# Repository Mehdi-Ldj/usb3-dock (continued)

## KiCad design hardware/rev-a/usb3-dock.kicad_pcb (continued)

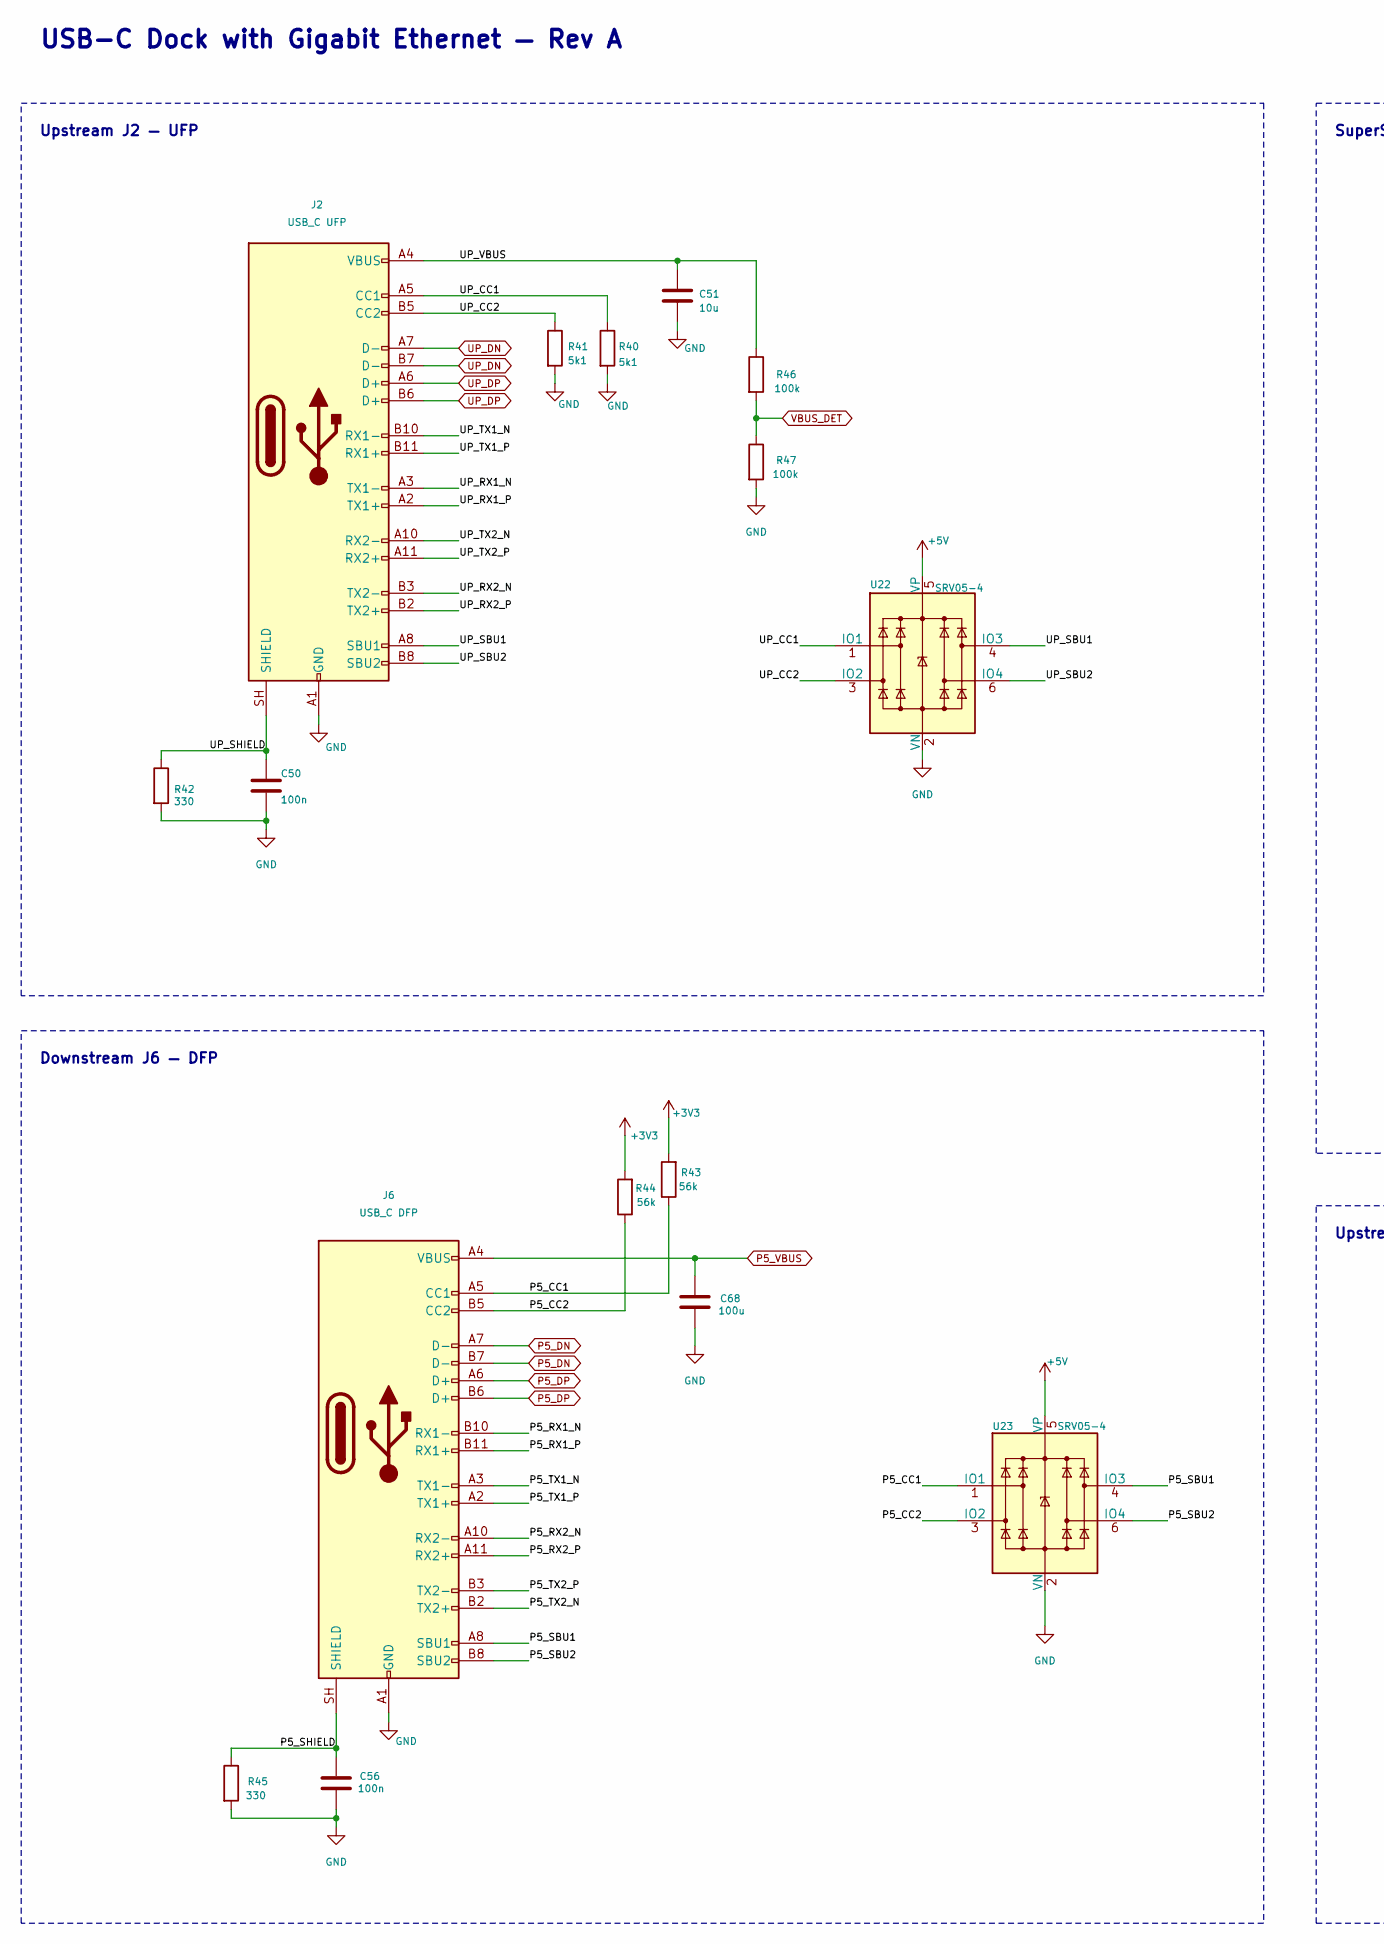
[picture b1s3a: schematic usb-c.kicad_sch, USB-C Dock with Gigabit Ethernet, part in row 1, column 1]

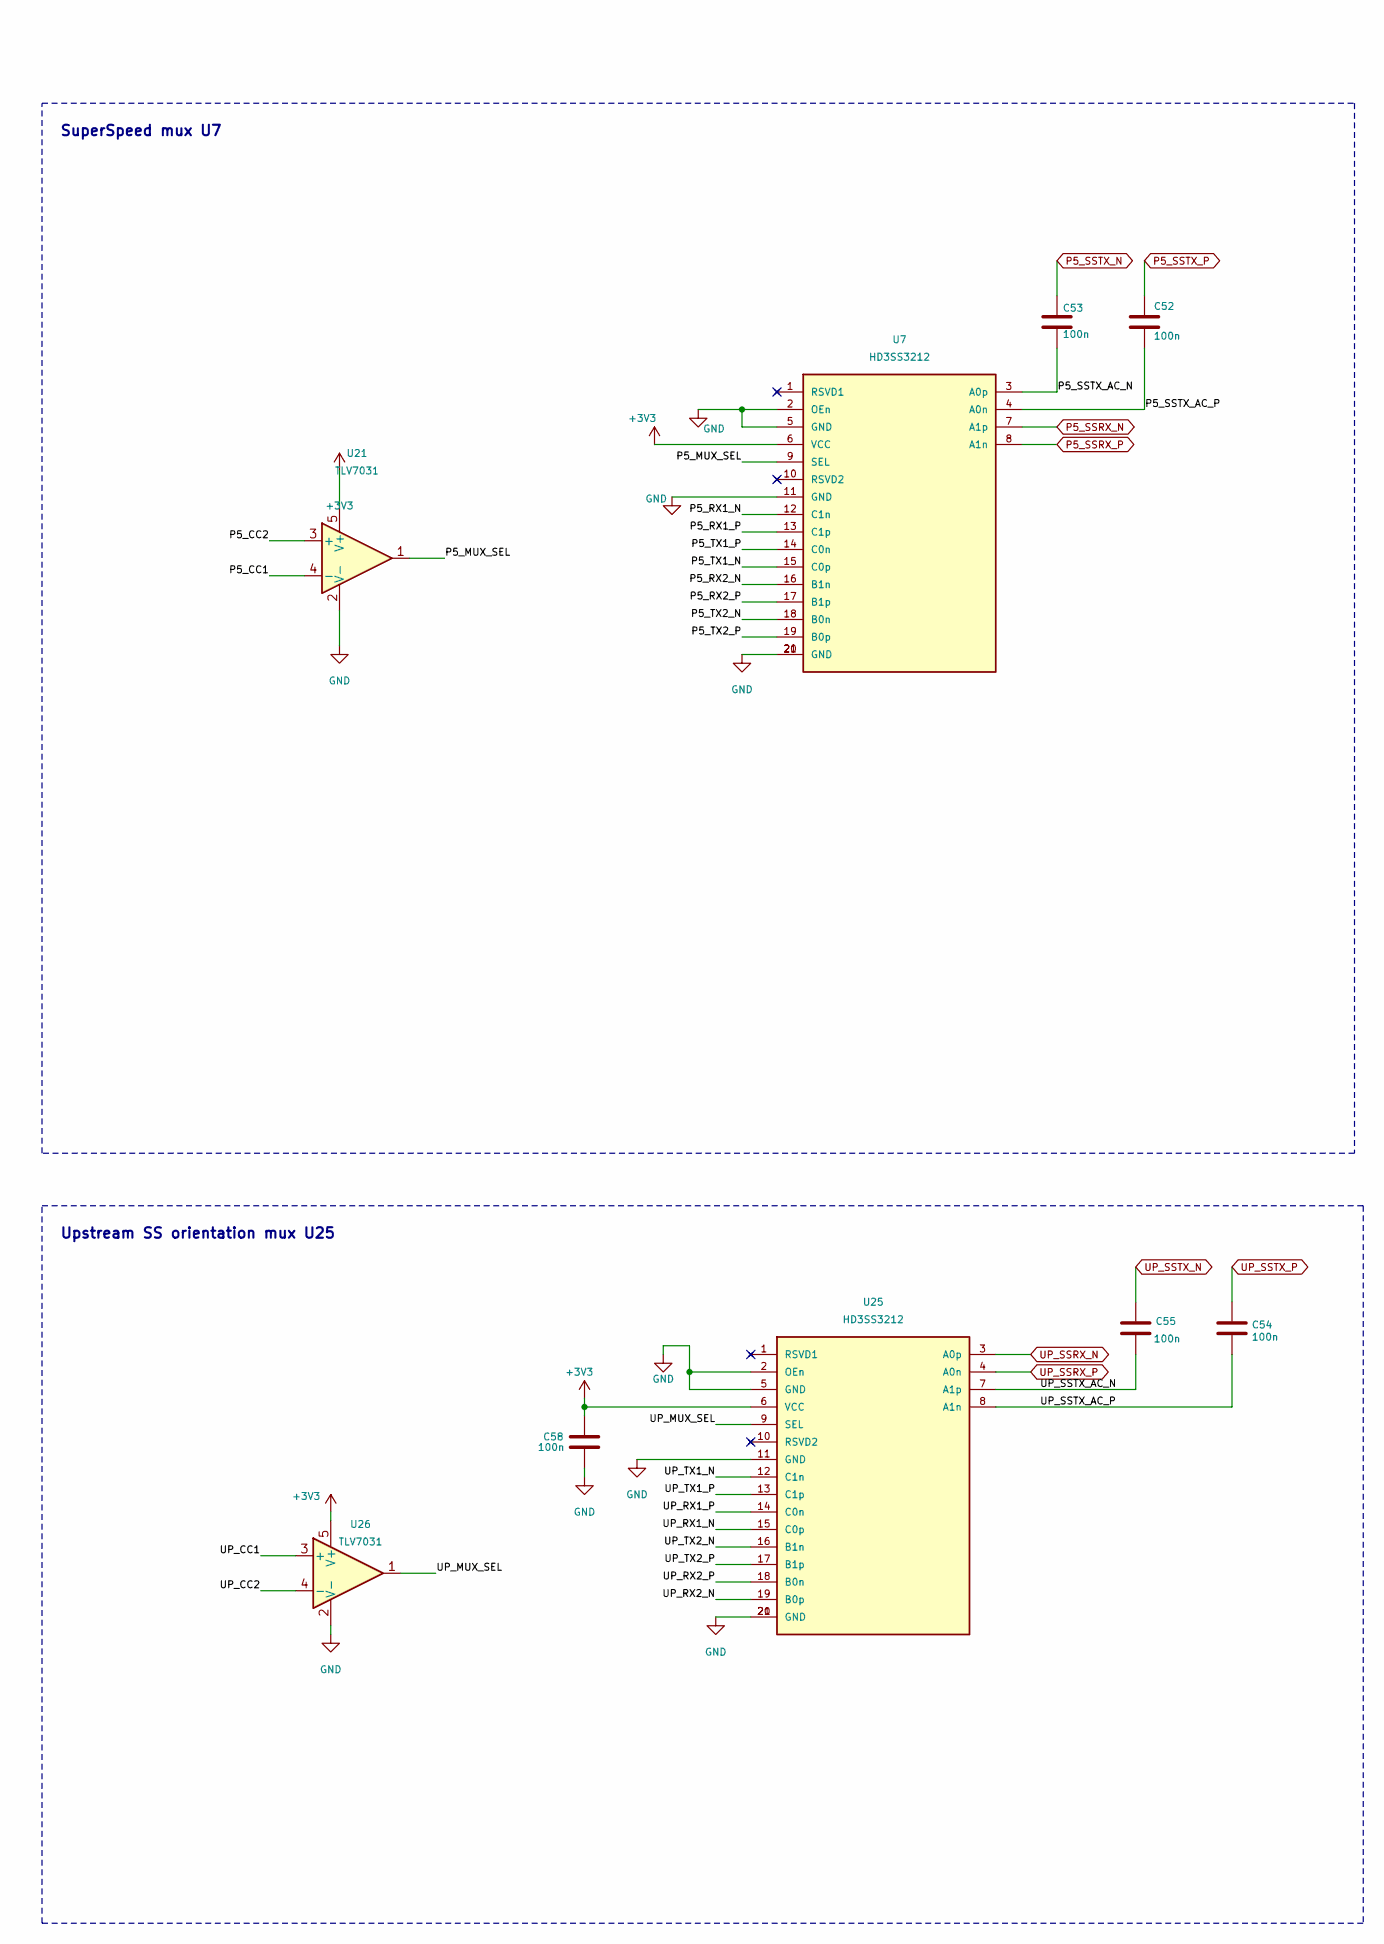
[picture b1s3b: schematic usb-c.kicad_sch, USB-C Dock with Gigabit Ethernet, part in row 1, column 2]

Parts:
C50, C52, C53, C54, C55, C56, C58: 100n; C_0402_1005Metric
C51: 10u; C_0805_2012Metric
C68: 100u; C_1210_3225Metric
J2: USB_C UFP; USB_C_Receptacle_Amphenol_12401610E4-2A
J6: USB_C DFP; USB_C_Receptacle_Amphenol_12401610E4-2A
R40, R41: 5k1; R_0603_1608Metric
R42, R45: 330; R_0603_1608Metric
R43, R44: 56k; R_0603_1608Metric
R46, R47: 100k; R_0603_1608Metric
U7, U25: HD3SS3212; DHVQFN-20-1EP_2.5x4.5mm_P0.5mm_EP1x3mm_TI
U21, U26: TLV7031; SOT-23-5
U22, U23: SRV05-4; SOT-23-6

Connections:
+3V3: C58.1, R43.2, R44.2, U7.6 (VCC), U21.5 (V+), U25.6 (VCC), U26.5 (V+); also elsewhere on the board
+5V: U22.5 (VP), U23.5 (VP); also elsewhere on the board
/usb-c/P5_CC1: J6.A5 (CC1), R43.1, U21.4 (-), U23.1 (IO1)
/usb-c/P5_CC2: J6.B5 (CC2), R44.1, U21.3 (+), U23.3 (IO2)
/usb-c/P5_MUX_SEL: U7.9 (SEL), U21.1
/usb-c/P5_RX1_N: J6.B10 (RX1-), U7.12 (C1n)
/usb-c/P5_RX1_P: J6.B11 (RX1+), U7.13 (C1p)
/usb-c/P5_RX2_N: J6.A10 (RX2-), U7.16 (B1n)
/usb-c/P5_RX2_P: J6.A11 (RX2+), U7.17 (B1p)
/usb-c/P5_SBU1: J6.A8 (SBU1), U23.4 (IO3)
/usb-c/P5_SBU2: J6.B8 (SBU2), U23.6 (IO4)
/usb-c/P5_SHIELD: C56.1, J6.SH (SHIELD), R45.1
/usb-c/P5_SSTX_AC_N: C53.2, U7.3 (A0p)
/usb-c/P5_SSTX_AC_P: C52.2, U7.4 (A0n)
/usb-c/P5_TX1_N: J6.A3 (TX1-), U7.15 (C0p)
/usb-c/P5_TX1_P: J6.A2 (TX1+), U7.14 (C0n)
/usb-c/P5_TX2_N: J6.B2 (TX2+), U7.18 (B0n)
/usb-c/P5_TX2_P: J6.B3 (TX2-), U7.19 (B0p)
/usb-c/UP_CC1: J2.A5 (CC1), R40.1, U22.1 (IO1), U26.3 (+)
/usb-c/UP_CC2: J2.B5 (CC2), R41.1, U22.3 (IO2), U26.4 (-)
/usb-c/UP_MUX_SEL: U25.9 (SEL), U26.1
/usb-c/UP_RX1_N: J2.A3 (TX1-), U25.15 (C0p)
/usb-c/UP_RX1_P: J2.A2 (TX1+), U25.14 (C0n)
/usb-c/UP_RX2_N: J2.B3 (TX2-), U25.19 (B0p)
/usb-c/UP_RX2_P: J2.B2 (TX2+), U25.18 (B0n)
/usb-c/UP_SBU1: J2.A8 (SBU1), U22.4 (IO3)
/usb-c/UP_SBU2: J2.B8 (SBU2), U22.6 (IO4)
/usb-c/UP_SHIELD: C50.1, J2.SH (SHIELD), R42.1
/usb-c/UP_SSTX_AC_N: C55.2, U25.7 (A1p)
/usb-c/UP_SSTX_AC_P: C54.2, U25.8 (A1n)
/usb-c/UP_TX1_N: J2.B10 (RX1-), U25.12 (C1n)
/usb-c/UP_TX1_P: J2.B11 (RX1+), U25.13 (C1p)
/usb-c/UP_TX2_N: J2.A10 (RX2-), U25.16 (B1n)
/usb-c/UP_TX2_P: J2.A11 (RX2+), U25.17 (B1p)
/usb-c/UP_VBUS: C51.1, J2.A4 (VBUS), J2.A9 (VBUS), J2.B4 (VBUS), J2.B9 (VBUS), R46.1
GND: C50.2, C51.2, C56.2, C58.2, C68.2, J2.A1 (GND), J2.A12 (GND), J2.B1 (GND), J2.B12 (GND), J6.A1 (GND), J6.A12 (GND), J6.B1 (GND), J6.B12 (GND), R40.2, R41.2, R42.2, R45.2, R47.2, U7.2 (OEn), U7.5 (GND), U7.11 (GND), U7.20 (GND), U7.21 (GND), U21.2 (V-), U22.2 (VN), U23.2 (VN), U25.2 (OEn), U25.5 (GND), U25.11 (GND), U25.20 (GND), U25.21 (GND), U26.2 (V-); also elsewhere on the board
P5_DN: J6.A7 (D-), J6.B7 (D-); also elsewhere on the board
P5_DP: J6.A6 (D+), J6.B6 (D+); also elsewhere on the board
P5_SSRX_N: U7.7 (A1p); also elsewhere on the board
P5_SSRX_P: U7.8 (A1n); also elsewhere on the board
P5_SSTX_N: C53.1; also elsewhere on the board
P5_SSTX_P: C52.1; also elsewhere on the board
P5_VBUS: C68.1, J6.A4 (VBUS), J6.A9 (VBUS), J6.B4 (VBUS), J6.B9 (VBUS); also elsewhere on the board
UP_DN: J2.A7 (D-), J2.B7 (D-); also elsewhere on the board
UP_DP: J2.A6 (D+), J2.B6 (D+); also elsewhere on the board
UP_SSRX_N: U25.3 (A0p); also elsewhere on the board
UP_SSRX_P: U25.4 (A0n); also elsewhere on the board
UP_SSTX_N: C55.1; also elsewhere on the board
UP_SSTX_P: C54.1; also elsewhere on the board
VBUS_DET: R46.2, R47.1; also elsewhere on the board

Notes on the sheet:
Downstream J6 — DFP
Upstream J2 — UFP
USB-C Dock with Gigabit Ethernet — Rev A
SuperSpeed mux U7
Upstream SS orientation mux U25

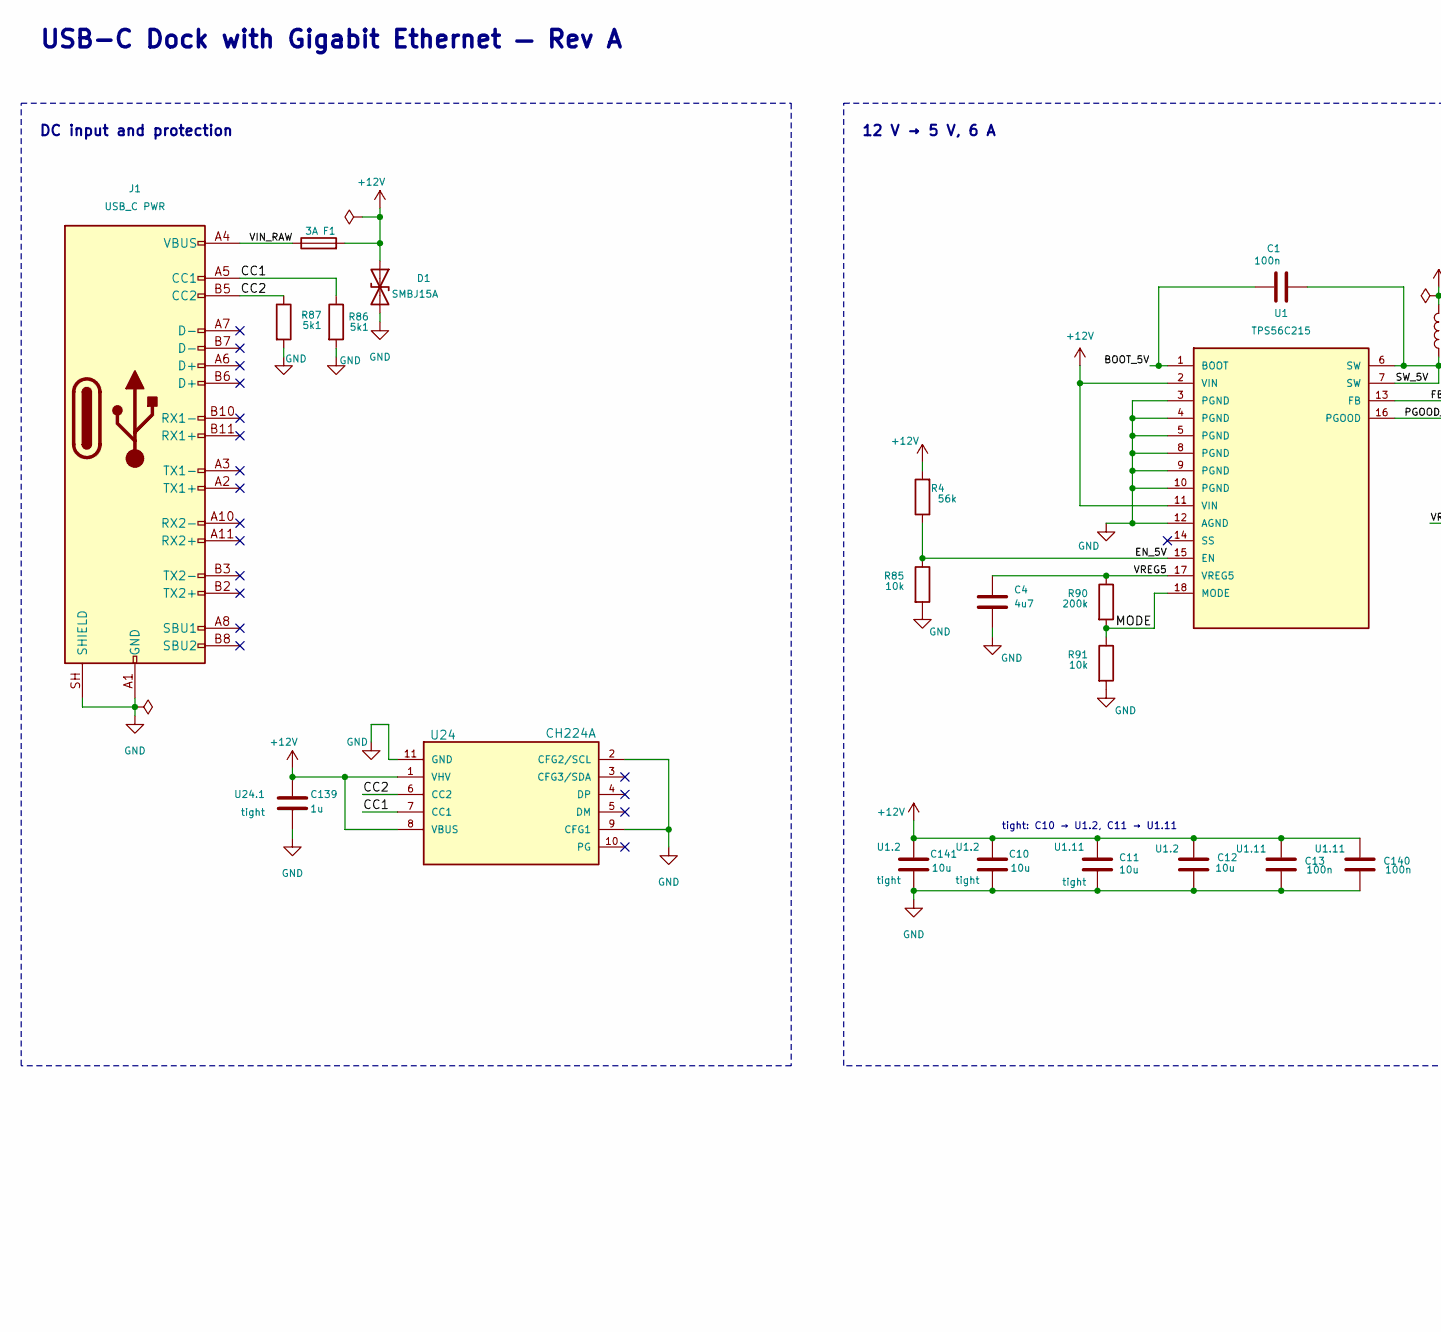
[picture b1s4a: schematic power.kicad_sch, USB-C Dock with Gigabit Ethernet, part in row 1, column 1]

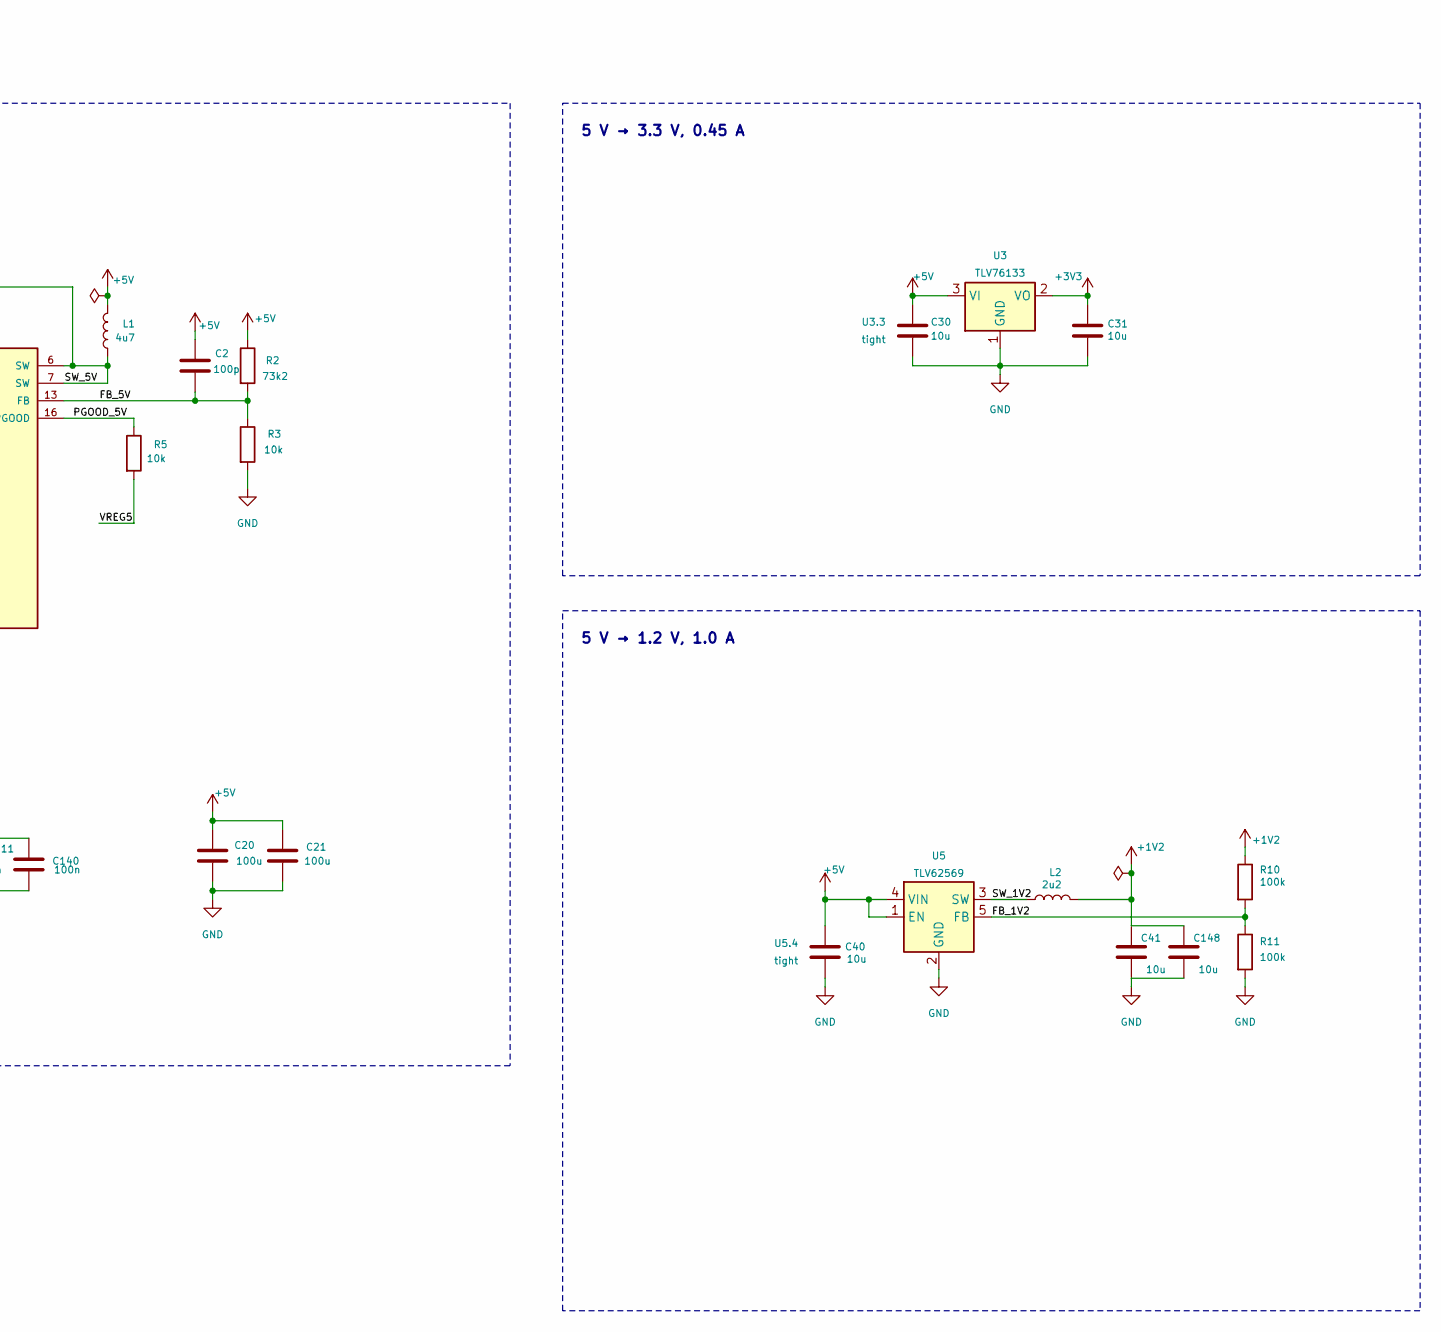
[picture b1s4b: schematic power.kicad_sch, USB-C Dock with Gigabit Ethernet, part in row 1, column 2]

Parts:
C1, C13, C140: 100n; C_0402_1005Metric
C2: 100p; C_0402_1005Metric
C4: 4u7; C_0603_1608Metric
C10, C11, C12, C30, C31, C40, C41, C141, C148: 10u; C_0805_2012Metric
C20, C21: 100u; C_1210_3225Metric
C139: 1u; C_0805_2012Metric
D1: SMBJ15A; D_SMB
F1: 3A; Fuse_1206_3216Metric
J1: USB_C PWR; USB_C_Receptacle_Amphenol_12401610E4-2A
L1: 4u7; L_7.1x6.6mm_CMLO0650H
L2: 2u2; L_4x4mm_PNR4020
R2: 73k2; R_0603_1608Metric
R3, R5, R85, R91: 10k; R_0603_1608Metric
R4: 56k; R_0603_1608Metric
R10, R11: 100k; R_0603_1608Metric
R86, R87: 5k1; R_0603_1608Metric
R90: 200k; R_0603_1608Metric
U1: TPS56C215; Texas_RNN0018A_TPS56C215
U3: TLV76133; SOT-223-3_TabPin2
U5: TLV62569; SOT-23-5
U24: CH224A; SSOP-10-1EP_3.9x4.9mm_P1mm_EP2.1x3.3mm

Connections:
+1V2: C41.1, C148.1, L2.2, R10.1; also elsewhere on the board
+3V3: C31.1, U3.2 (VO); also elsewhere on the board
+5V: C2.1, C20.1, C21.1, C30.1, C40.1, L1.2, R2.1, U3.3 (VI), U5.1 (EN), U5.4 (VIN); also elsewhere on the board
+12V: C10.1, C11.1, C12.1, C13.1, C139.1, C140.1, C141.1, D1.1 (A1), F1.2, R4.2, U1.2 (VIN), U1.11 (VIN), U24.1 (VHV), U24.8 (VBUS)
/power/BOOT_5V: C1.1, U1.1 (BOOT)
/power/CC1: J1.A5 (CC1), R86.1, U24.7 (CC1)
/power/CC2: J1.B5 (CC2), R87.1, U24.6 (CC2)
/power/EN_5V: R4.1, R85.1, U1.15 (EN)
/power/FB_1V2: R10.2, R11.1, U5.5 (FB)
/power/FB_5V: C2.2, R2.2, R3.1, U1.13 (FB)
/power/MODE: R90.2, R91.1, U1.18 (MODE)
/power/PGOOD_5V: R5.1, U1.16 (PGOOD)
/power/SW_1V2: L2.1, U5.3 (SW)
/power/SW_5V: C1.2, L1.1, U1.6 (SW), U1.7 (SW)
/power/VIN_RAW: F1.1, J1.A4 (VBUS), J1.A9 (VBUS), J1.B4 (VBUS), J1.B9 (VBUS)
/power/VREG5: C4.1, R5.2, R90.1, U1.17 (VREG5)
GND: C4.2, C10.2, C11.2, C12.2, C13.2, C20.2, C21.2, C30.2, C31.2, C40.2, C41.2, C139.2, C140.2, C141.2, C148.2, D1.2 (A2), J1.A1 (GND), J1.A12 (GND), J1.B1 (GND), J1.B12 (GND), J1.SH (SHIELD), R3.2, R11.2, R85.2, R86.2, R87.2, R91.2, U1.3 (PGND), U1.4 (PGND), U1.5 (PGND), U1.8 (PGND), U1.9 (PGND), U1.10 (PGND), U1.12 (AGND), U3.1 (GND), U5.2 (GND), U24.2 (CFG2/SCL), U24.9 (CFG1), U24.11 (GND); also elsewhere on the board

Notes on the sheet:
USB-C Dock with Gigabit Ethernet — Rev A
12 V → 5 V, 6 A
tight: C10 → U1.2, C11 → U1.11
5 V → 3.3 V, 0.45 A
5 V → 1.2 V, 1.0 A
DC input and protection

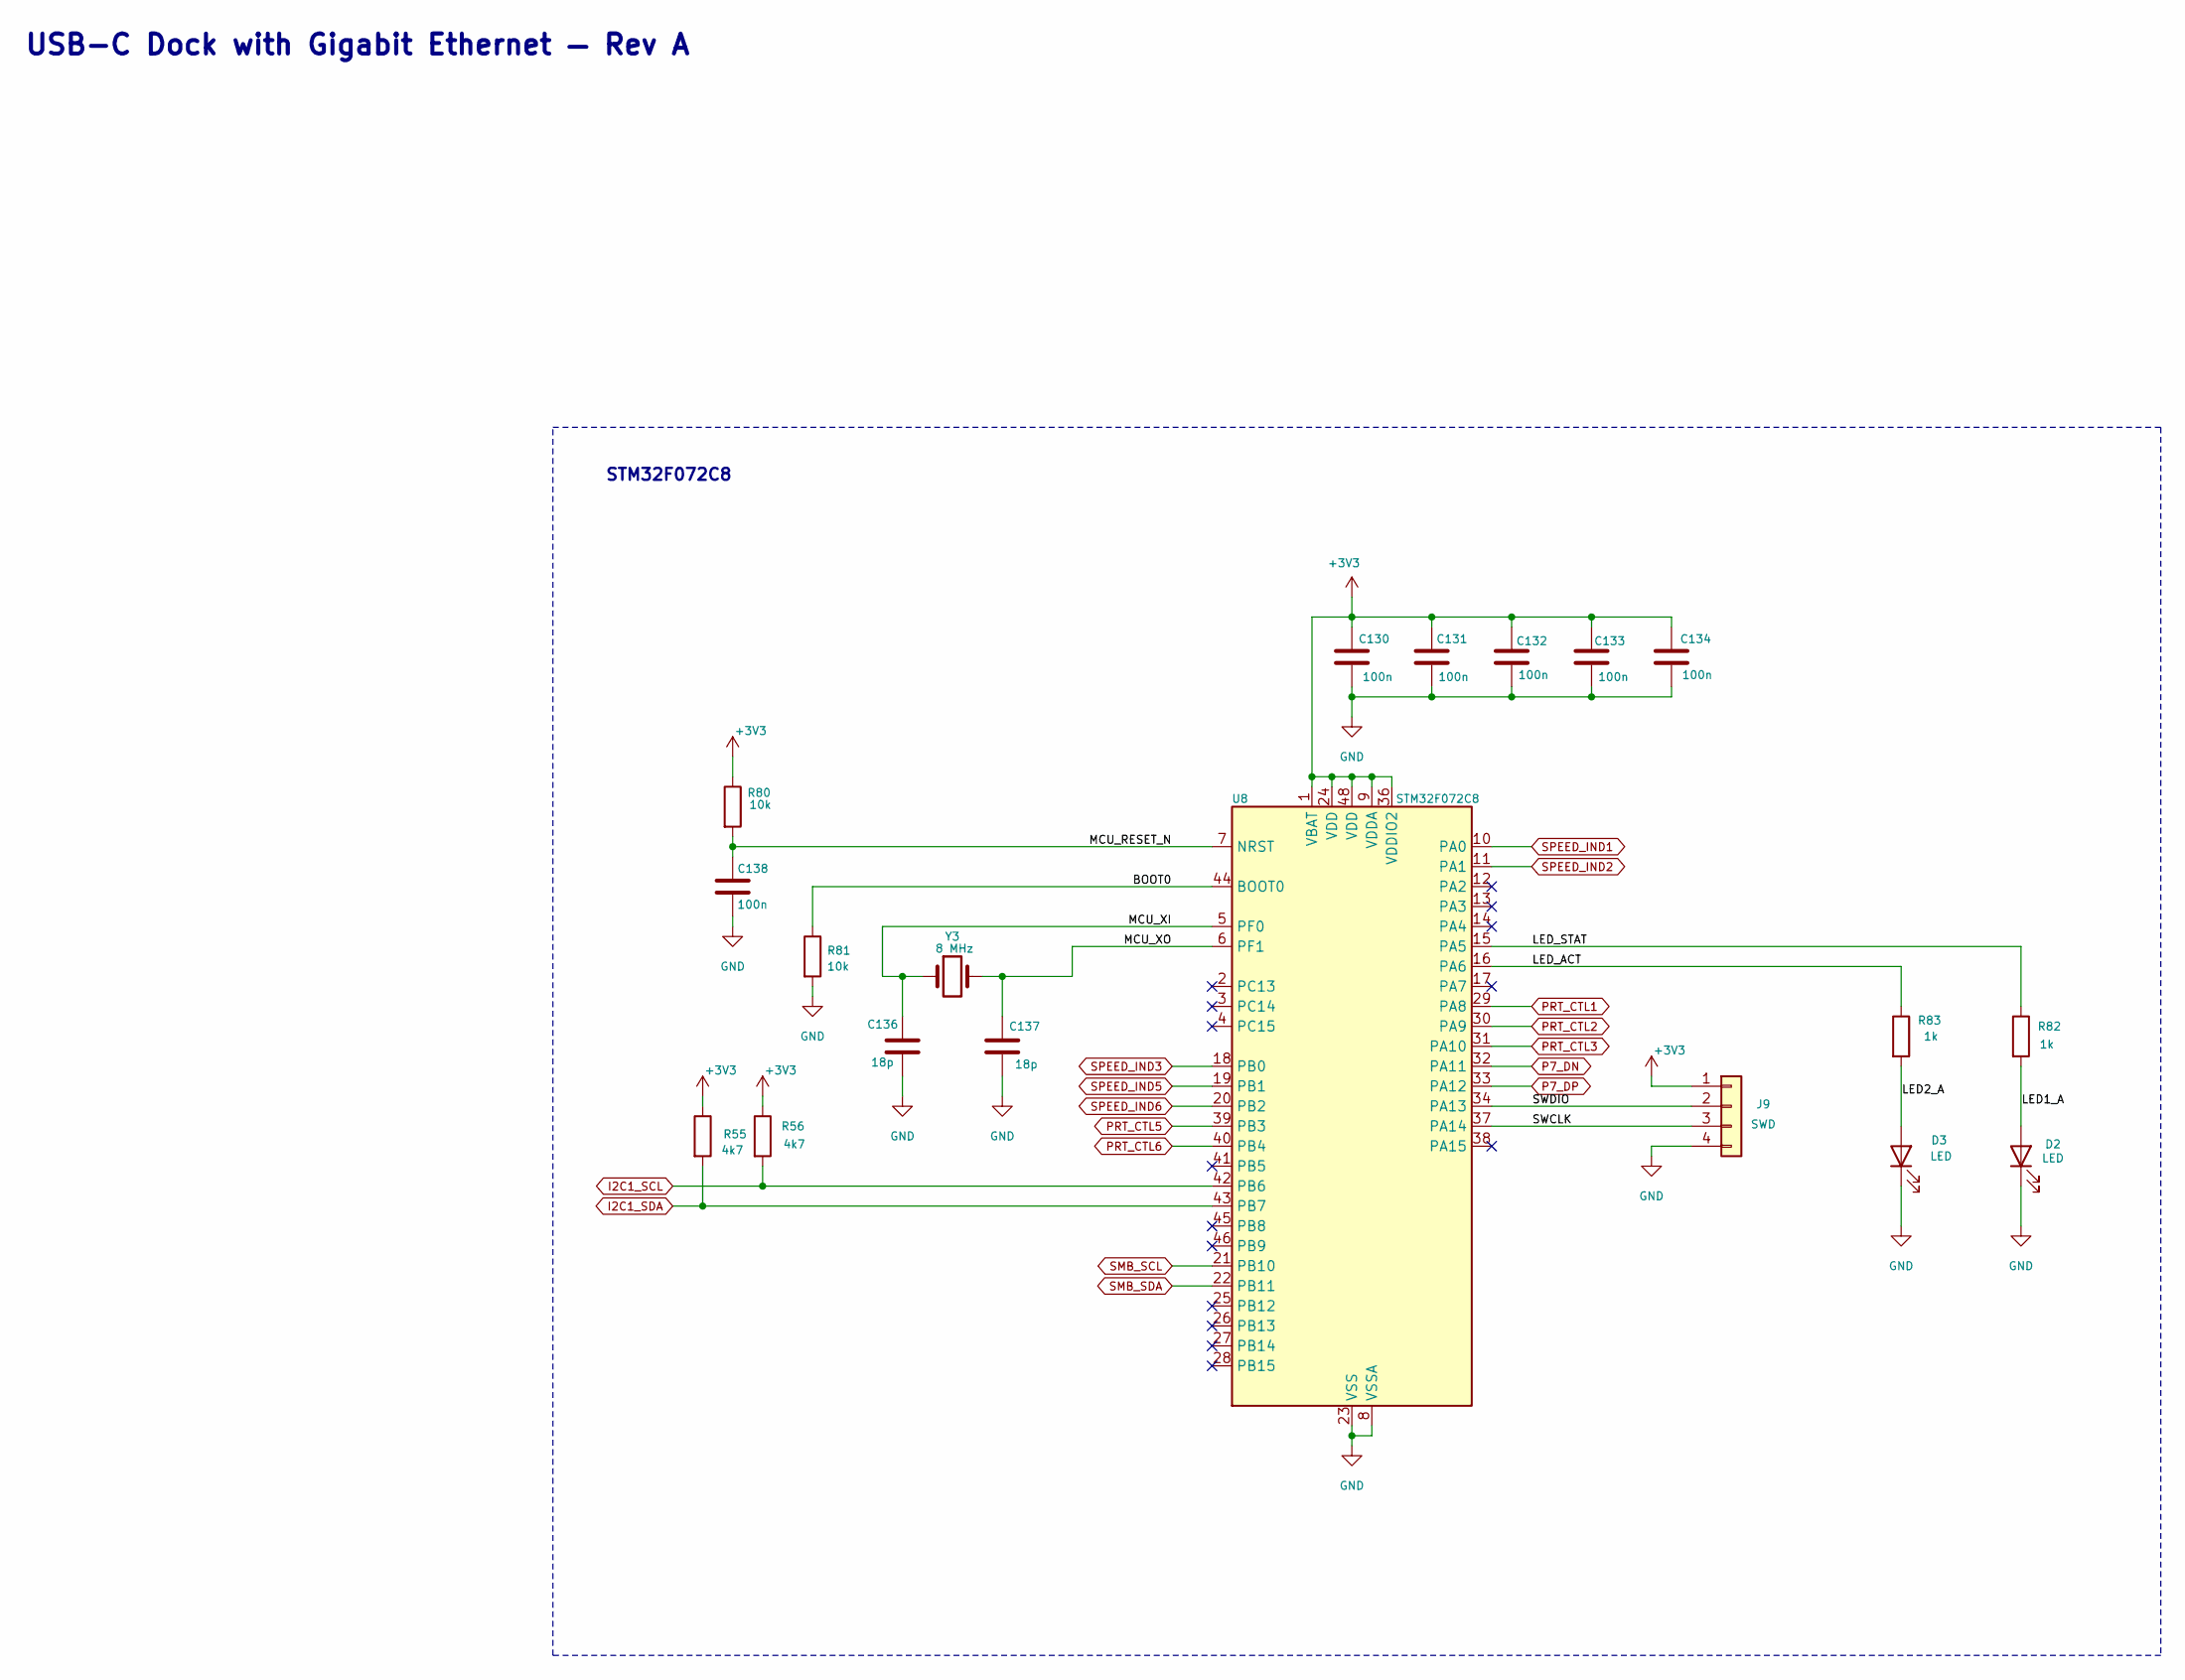
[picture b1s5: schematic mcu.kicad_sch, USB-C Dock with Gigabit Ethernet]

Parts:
C130, C131, C132, C133, C134, C138: 100n; C_0402_1005Metric
C136, C137: 18p; C_0402_1005Metric
D2, D3: LED; LED_0603_1608Metric
J9: SWD; PinHeader_1x04_P2.54mm_Vertical
R55, R56: 4k7; R_0603_1608Metric
R80, R81: 10k; R_0603_1608Metric
R82, R83: 1k; R_0603_1608Metric
U8: STM32F072C8; LQFP-48_7x7mm_P0.5mm
Y3: 8 MHz; Crystal_SMD_5032-2Pin_5.0x3.2mm

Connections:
+3V3: C130.1, C131.1, C132.1, C133.1, C134.1, J9.1, R55.1, R56.1, R80.1, U8.1 (VBAT), U8.9 (VDDA), U8.24 (VDD), U8.36 (VDDIO2), U8.48 (VDD); also elsewhere on the board
/mcu/BOOT0: R81.1, U8.44 (BOOT0)
/mcu/LED1_A: D2.2 (A), R82.2
/mcu/LED2_A: D3.2 (A), R83.2
/mcu/LED_ACT: R83.1, U8.16 (PA6)
/mcu/LED_STAT: R82.1, U8.15 (PA5)
/mcu/MCU_RESET_N: C138.1, R80.2, U8.7 (NRST)
/mcu/MCU_XI: C136.1, U8.5 (PF0), Y3.1
/mcu/MCU_XO: C137.1, U8.6 (PF1), Y3.2
/mcu/SWCLK: J9.3, U8.37 (PA14)
/mcu/SWDIO: J9.2, U8.34 (PA13)
GND: C130.2, C131.2, C132.2, C133.2, C134.2, C136.2, C137.2, C138.2, D2.1 (K), D3.1 (K), J9.4, R81.2, U8.8 (VSSA), U8.23 (VSS), U8.35 (VSS), U8.47 (VSS); also elsewhere on the board
I2C1_SCL: R56.2, U8.42 (PB6); also elsewhere on the board
I2C1_SDA: R55.2, U8.43 (PB7); also elsewhere on the board
P7_DN: U8.32 (PA11); also elsewhere on the board
P7_DP: U8.33 (PA12); also elsewhere on the board
PRT_CTL1: U8.29 (PA8); also elsewhere on the board
PRT_CTL2: U8.30 (PA9); also elsewhere on the board
PRT_CTL3: U8.31 (PA10); also elsewhere on the board
PRT_CTL5: U8.39 (PB3); also elsewhere on the board
PRT_CTL6: U8.40 (PB4); also elsewhere on the board
SMB_SCL: U8.21 (PB10); also elsewhere on the board
SMB_SDA: U8.22 (PB11); also elsewhere on the board
SPEED_IND1: U8.10 (PA0); also elsewhere on the board
SPEED_IND2: U8.11 (PA1); also elsewhere on the board
SPEED_IND3: U8.18 (PB0); also elsewhere on the board
SPEED_IND5: U8.19 (PB1); also elsewhere on the board
SPEED_IND6: U8.20 (PB2); also elsewhere on the board

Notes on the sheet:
USB-C Dock with Gigabit Ethernet — Rev A
STM32F072C8
